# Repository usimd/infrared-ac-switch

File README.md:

# IR-based remote AC switch
This projects aims to remote control an AC power socket. It features two PCBs with one being an IR emitter controlled by an AC input and a receiver/switch that turns on power if the IR signal is received.

The motivation to build this was an existing power outlet at the ceiling of our kitchen being controlled by a wall switch which I wanted to use to switch another lighting device in the room powered from a wall socket.
The emitter is mounted at the ceiling outlet and turned on once the wall switch was used. The receiver then turns on the lighting device at the other end of the room as long as the emitter keeps signalling.

## Circuits
Both circuits implement a capacitor power supply, as only a few mA of current are reqired to either drive an LED and a signal generator (emitter) or the IR receiver and a solid state relay (switch). The capacitor PSU is tolerant up to 230V AC.

The IR signal is pulsed at 38kHz and can be tuned using a potentiometer on the emitter's side. The signal is generated using a simple 555 circuit.

If you want to enclose the receiver/switch, there's a [case available to 3D print](case/case.3mf).

## Safety note
I am no electronics specialist and can not guarantee for the safety of these devices. If you want to build these for yourself be aware that you'll be working with mains voltage which can be potentially deadly when handled without care! Use at your own risk.

The PCBs have been prototyped at AISLER:
* [switch](https://aisler.net/p/HPFIOOUA)
* [emitter](https://aisler.net/p/JRNHJFBC)

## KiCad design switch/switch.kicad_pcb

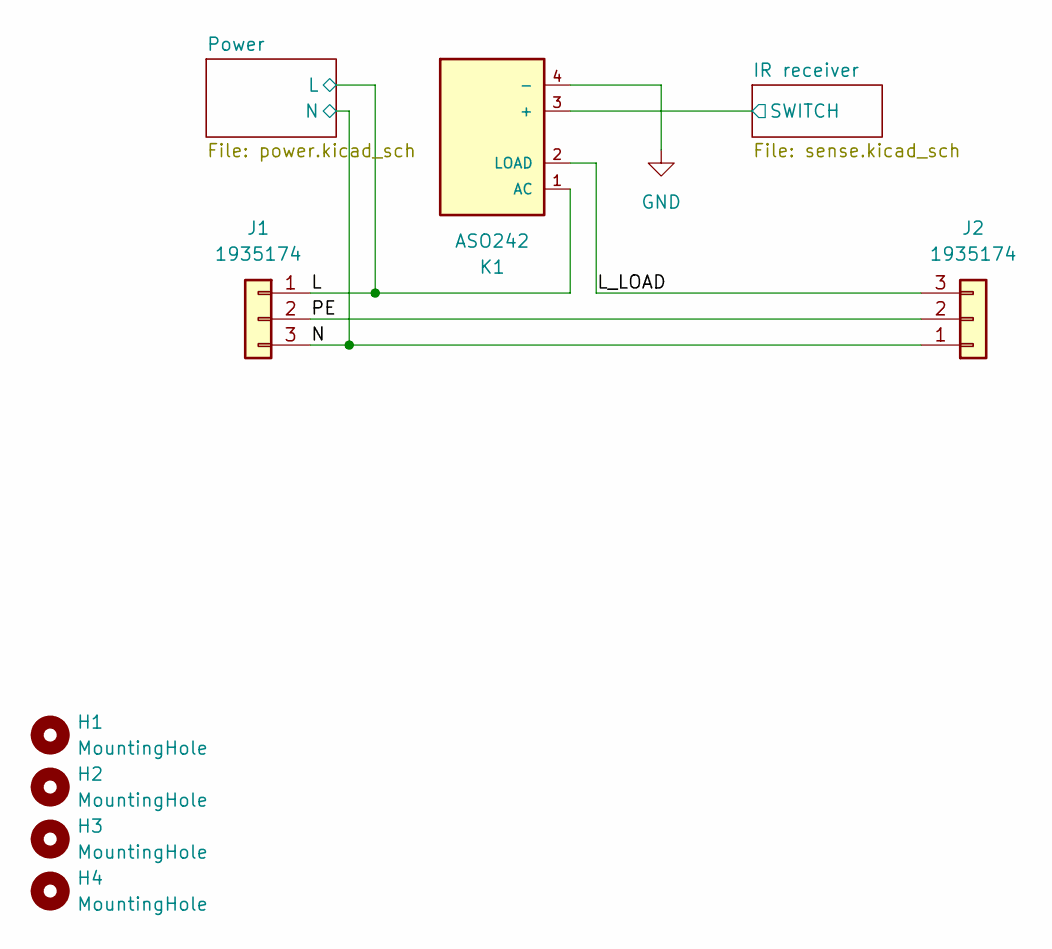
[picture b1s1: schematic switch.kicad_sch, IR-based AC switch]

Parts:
H1, H2, H3, H4: MountingHole; MountingHole_2.2mm_M2_ISO14580
J1, J2: 1935174; TerminalBlock_Phoenix_PT-1,5-3-5.0-H_1x03_P5.00mm_Horizontal; MPN1 Phoenix Contact:1935174
K1: ASO242; MPN ASO242; DigiKey_Part_Number CC1336-ND

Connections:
/IR receiver/SWITCH: K1.3 (+); also elsewhere on the board
/L: J1.1, K1.1 (AC); also elsewhere on the board
/L_LOAD: J2.3, K1.2 (LOAD)
/N: J1.3, J2.1; also elsewhere on the board
/PE: J1.2, J2.2
GND: K1.4 (-); also elsewhere on the board

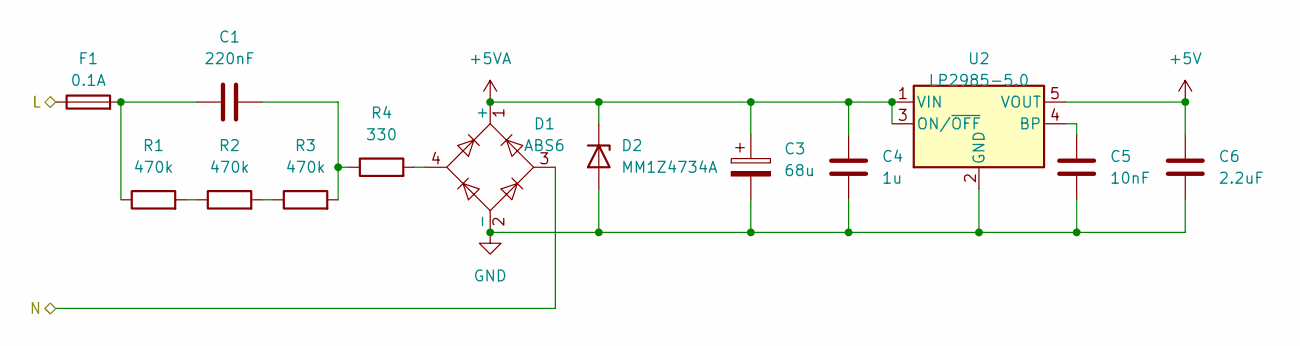
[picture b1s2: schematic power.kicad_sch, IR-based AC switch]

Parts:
C1: 220nF; C_Rect_L18.0mm_W8.0mm_P15.00mm_FKS3_FKP3; MPN1 WIMA:MKX2AW32205B00KSSD
C3: 68u; CP_Elec_10x12.5; MPN1 Panasonic:50SVPF68M
C4: 1u; C_0603_1608Metric; MPN1 Kyovera AVX:0603YD105KAT2A
C5: 10nF; C_0805_2012Metric
C6: 2.2uF; C_0805_2012Metric
D1: ABS6; Diode_Bridge_Diotec_ABS; MPN1 Diotec:ABS6
D2: MM1Z4734A; D_SOD-123F; MPN1 Diotec:MM1Z4734A
F1: 0.1A; Fuse_Littelfuse_395Series; MPN1 ESKA:883007-1
R1, R2, R3: 470k; R_0805_2012Metric_Pad1.20x1.40mm_HandSolder
R4: 330; R_Axial_DIN0516_L15.5mm_D5.0mm_P7.62mm_Vertical; MPN1 Vitrohm:CRF253-45T330R
U2: LP2985-5.0; SOT-23-5; MPN1 Texas Instruments:LP2985-50DBVR

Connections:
+5V: C6.1, U2.5 (VOUT); also elsewhere on the board
+5VA: C3.1, C4.1, D1.1 (+), D2.1 (K), U2.1 (VIN), U2.3 (ON/~OFF)
/L: F1.1; also elsewhere on the board
/N: D1.3; also elsewhere on the board
GND: C3.2, C4.2, C5.2, C6.2, D1.2 (-), D2.2 (A), U2.2 (GND); also elsewhere on the board
unnamed: C1.1, F1.2, R1.1
unnamed: C1.2, R3.2, R4.1
unnamed: D1.4, R4.2
unnamed: R1.2, R2.1
unnamed: R2.2, R3.1
unnamed: C5.1, U2.4 (BP)

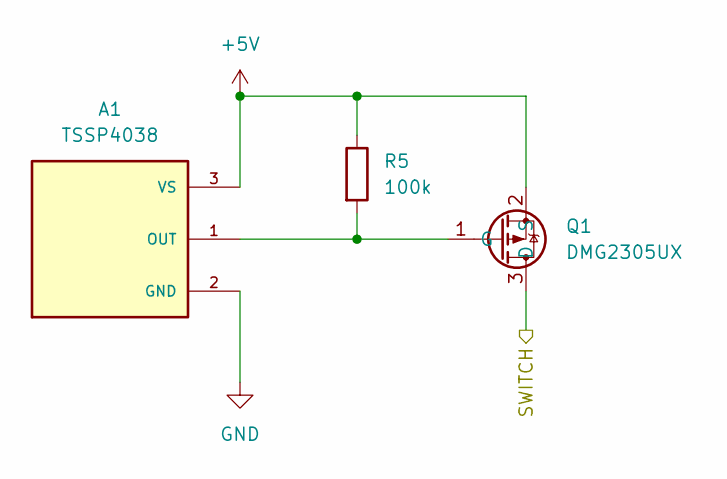
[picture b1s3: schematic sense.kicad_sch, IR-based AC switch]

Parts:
A1: TSSP4038; XDCR_TSSP4038; PARTREV 2.3
Q1: DMG2305UX; SOT-23; MPN1 Diodes:DMG2305UX-13
R5: 100k; R_0805_2012Metric

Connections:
+5V: A1.3 (VS), Q1.2 (S), R5.1; also elsewhere on the board
/IR receiver/SWITCH: Q1.3 (D); also elsewhere on the board
GND: A1.2 (GND); also elsewhere on the board
unnamed: A1.1 (OUT), Q1.1 (G), R5.2

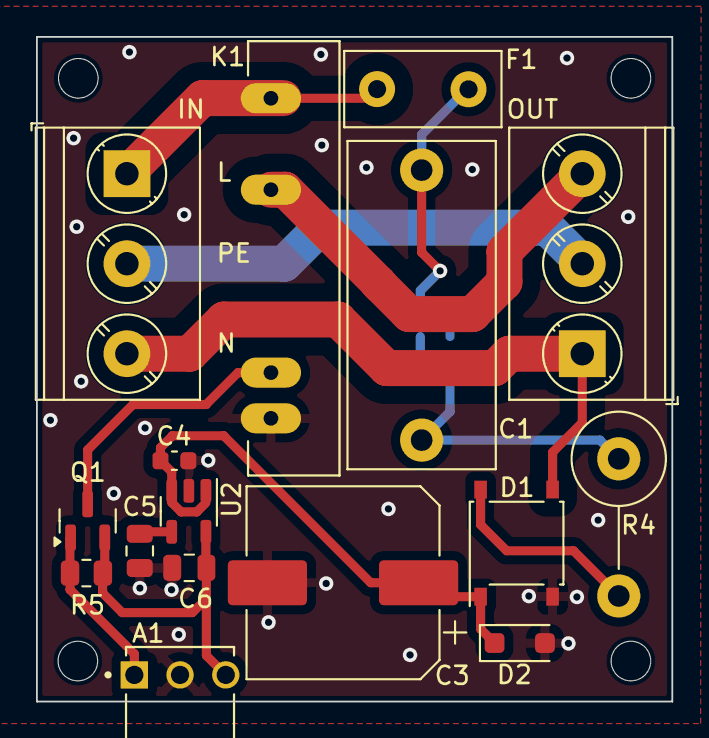
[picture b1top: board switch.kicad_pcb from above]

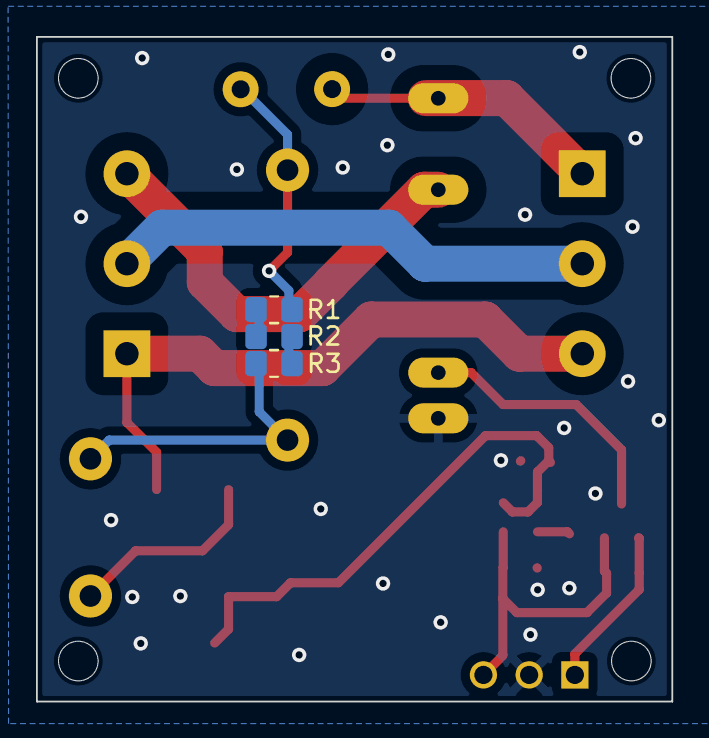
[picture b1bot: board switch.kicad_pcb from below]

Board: 2 copper layers, 35.3 x 36.9 mm, 23 parts (3 on the bottom side), 15 nets.

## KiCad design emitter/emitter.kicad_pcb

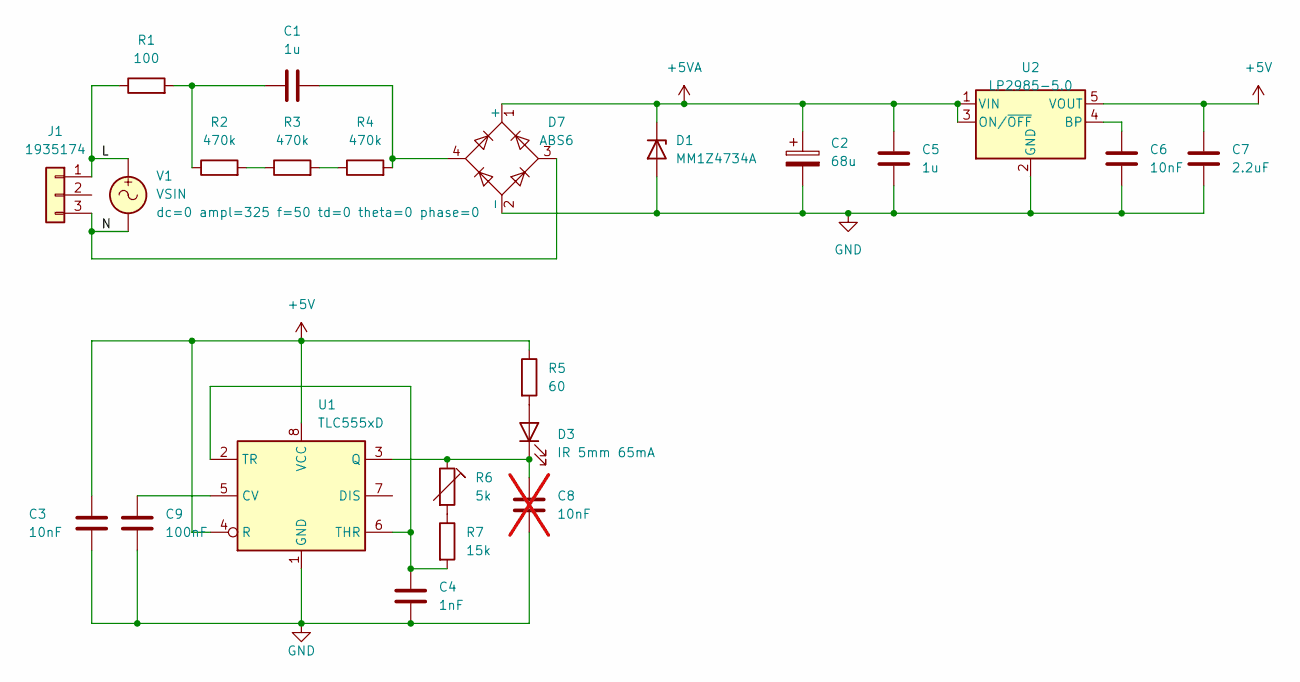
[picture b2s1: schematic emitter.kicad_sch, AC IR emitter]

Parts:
C1: 1u; C_Rect_L26.5mm_W10.5mm_P22.50mm_MKS4; MPN1 WIMA:MKX2AW41005I00KSSD
C2: 68u; CP_Elec_10x12.5; MPN1 Panasonic:50SVPF68M
C3, C6: 10nF; C_0805_2012Metric
C4: 1nF; C_0805_2012Metric
C5: 1u; C_0603_1608Metric
C7: 2.2uF; C_0805_2012Metric
C8: 10nF; C_0805_2012Metric; not fitted
C9: 100nF; C_0805_2012Metric
D1: MM1Z4734A; D_SOD-123F; MPN1 Diotec:MM1Z4734A
D3: IR 5mm 65mA; LED_D5.0mm; MPN1 Everlight:IR333
D7: ABS6; Diode_Bridge_Diotec_ABS; MPN1 Diotec:ABS6
J1: 1935174; TerminalBlock_Phoenix_PT-1,5-3-5.0-H_1x03_P5.00mm_Horizontal; MPN1 Phoenix Contact:1935174
R1: 100; R_Axial_DIN0516_L15.5mm_D5.0mm_P7.62mm_Vertical; MPN1 Vitrohm:CRF250JT-73-100RYY
R2, R3, R4: 470k; R_0603_1608Metric
R5: 60; R_0805_2012Metric; MPN1 Weltron:092305BTC
R6: 5k; Potentiometer_Bourns_3296W_Vertical; MPN1 Weltron:001045026338
R7: 15k; R_0603_1608Metric
U1: TLC555xD; SOIC-8_3.9x4.9mm_P1.27mm; MPN1 Texas Instruments:TLC555CDR
U2: LP2985-5.0; SOT-23-5; MPN1 Texas Instruments:LP2985-50DBVR
V1: VSIN

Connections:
+5V: C3.1, C7.1, R5.1, U1.4 (R), U1.8 (VCC), U2.5 (VOUT)
+5VA: C2.1, C5.1, D1.1 (K), D7.1 (+), U2.1 (VIN), U2.3 (ON/~OFF)
/L: J1.1, R1.1, V1.1
/N: D7.3, J1.3, V1.2
GND: C2.2, C3.2, C4.2, C5.2, C6.2, C7.2, C8.2, C9.2, D1.2 (A), D7.2 (-), U1.1 (GND), U2.2 (GND)
unnamed: C1.1, R1.2, R2.1
unnamed: C1.2, D7.4, R4.2
unnamed: D3.2 (A), R5.2
unnamed: C8.1, D3.1 (K), R6.1, U1.3 (Q)
unnamed: R2.2, R3.1
unnamed: R3.2, R4.1
unnamed: R6.2, R7.1
unnamed: C9.1, U1.5 (CV)
unnamed: C4.1, R7.2, U1.2 (TR), U1.6 (THR)
unnamed: C6.1, U2.4 (BP)

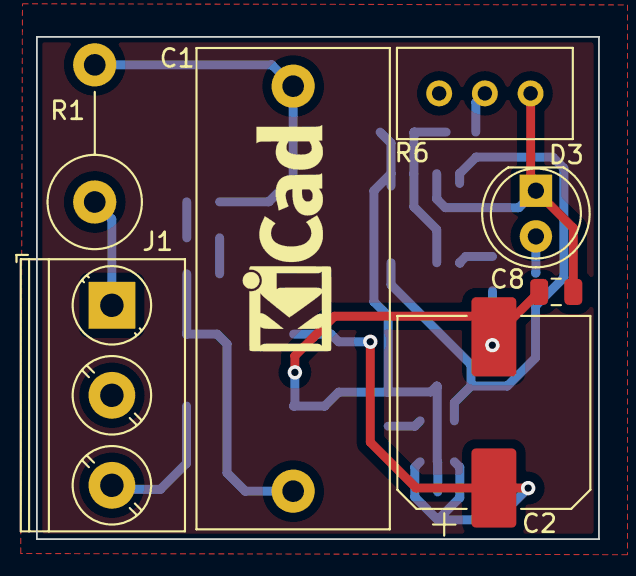
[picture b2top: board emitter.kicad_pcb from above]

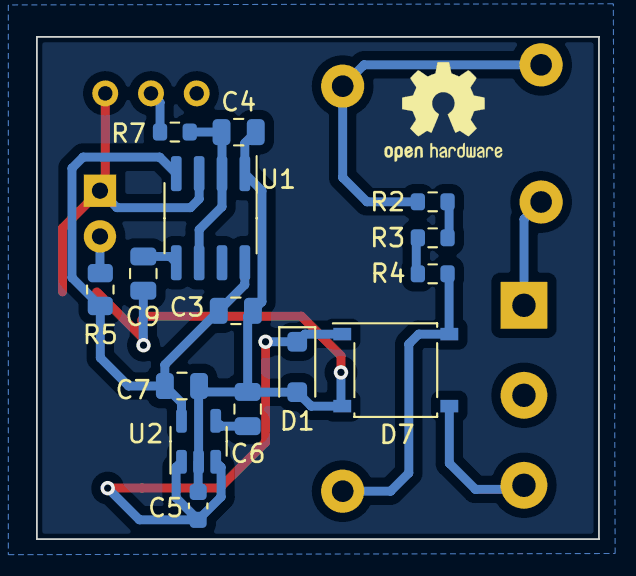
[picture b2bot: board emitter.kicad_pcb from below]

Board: 2 copper layers, 31.2 x 27.9 mm, 22 parts (15 on the bottom side), 15 nets.

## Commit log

2023-11-12 Initial import
2024-11-03 Updated rev
2025-01-06 Add case
2025-01-06 Add PCB images
2025-01-06 Fix issues
